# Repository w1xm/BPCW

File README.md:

# BPCW
1W UHF CW Trainer 

## Setup
The KiCAD project requires the W1MX-Parts project, see https://github.mit.edu/w1mx/W1MX-Parts.

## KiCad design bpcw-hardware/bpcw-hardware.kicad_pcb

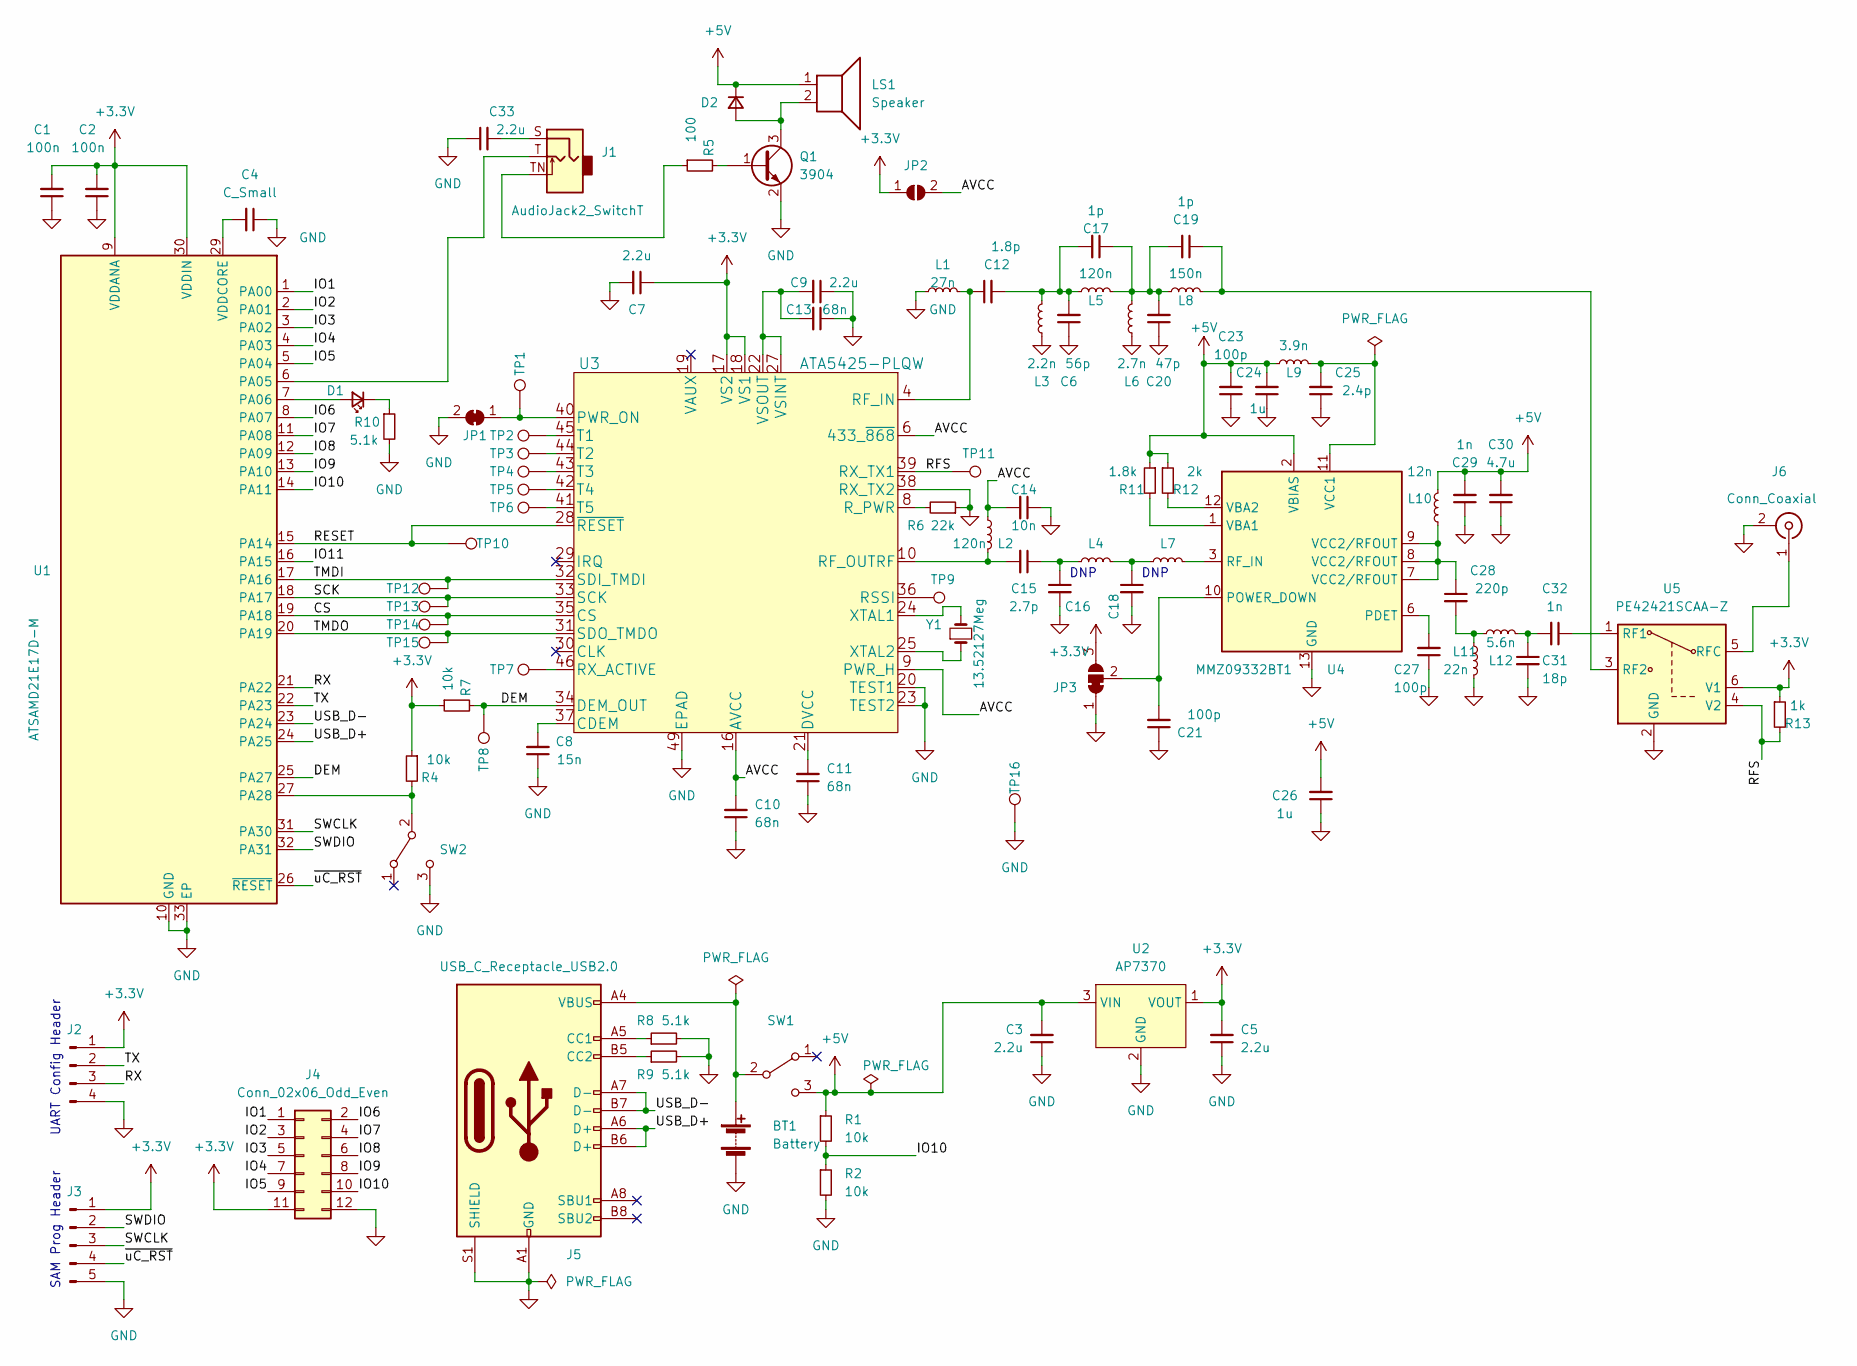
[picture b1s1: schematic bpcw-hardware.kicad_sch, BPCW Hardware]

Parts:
BT1: Battery; JST_XH_B2B-XH-A_1x02_P2.50mm_Vertical
C1, C2: 100n; C_0402_1005Metric
C3, C5, C7, C9, C33: 2.2u; C_0603_1608Metric
C4, C16, C18: C_Small; C_0402_1005Metric
C6: 56p; C_0402_1005Metric
C8: 15n; C_0402_1005Metric
C10, C11, C13: 68n; C_0402_1005Metric
C12: 1.8p; C_0402_1005Metric
C14: 10n; C_0402_1005Metric
C15: 2.7p; C_0402_1005Metric
C17, C19: 1p; C_0402_1005Metric
C20: 47p; C_0402_1005Metric
C21, C23, C27: 100p; C_0402_1005Metric
C24, C26: 1u; C_0603_1608Metric
C25: 2.4p; C_0402_1005Metric
C28: 220p; C_0402_1005Metric
C29, C32: 1n; C_0402_1005Metric
C30: 4.7u; C_0603_1608Metric
C31: 18p; C_0402_1005Metric
D1: LED_Small; LED_0603_1608Metric
D2: D_Small; D_SOD-323
J1: AudioJack2_SwitchT; CUI_MJ-3523-SMT
J2: Conn_01x04_Male; PinHeader_1x04_P2.54mm_Vertical
J3: Conn_01x05_Male; PinHeader_1x05_P2.54mm_Vertical
J4: Conn_02x06_Odd_Even; PinHeader_2x06_P2.54mm_Vertical
J5: USB_C_Receptacle_USB2.0; USB_C_Receptacle_GCT_USB4085
J6: Conn_Coaxial; SMA_Samtec_SMA-J-P-X-ST-EM1_EdgeMount
JP1: SolderJumper_2_Bridged; SolderJumper-2_P1.3mm_Bridged_Pad1.0x1.5mm
JP2: SolderJumper_2_Open; R_0402_1005Metric
JP3: SolderJumper_3_Bridged12; SolderJumper-3_P1.3mm_Bridged12_Pad1.0x1.5mm
L1: 27n; L_0603_1608Metric
L2, L5: 120n; L_0603_1608Metric
L3: 2.2n; L_0603_1608Metric
L4: 0; L_0603_1608Metric
L6: 2.7n; L_0603_1608Metric
L7, L9: 3.9n; L_0603_1608Metric
L8: 150n; L_0603_1608Metric
L10: 12n; L_0603_1608Metric
L11: 22n; L_0603_1608Metric
L12: 5.6n; L_0603_1608Metric
LS1: Speaker; CMT-9648-85T
Q1: 3904; SOT-23
R1, R2, R4, R7: 10k; R_0402_1005Metric
R5: 100; R_0402_1005Metric
R6: 22k; R_0402_1005Metric
R8, R9, R10: 5.1k; R_0402_1005Metric
R11: 1.8k; R_0402_1005Metric
R12: 2k; R_0402_1005Metric
R13: 1k; R_0402_1005Metric
SW1: SW_SPDT; 1825232-1; MPN 1825232-1
SW2: SW_SPDT; SS0750301F040P1A-Sideways; MPN 1825232-1
TP1, TP2, TP3, TP4, TP5, TP6, TP7, TP8, TP9, TP10, TP11, TP12, TP13, TP14, TP15, TP16: TestPoint; RCU-0603
U1: ATSAMD21E17D-M; QFN-32-1EP_5x5mm_P0.5mm_EP3.6x3.6mm
U2: AP7370; SOT-89-3
U3: ATA5425-PLQW; TQFN-48-1EP_7x7mm_P0.5mm_EP5.1x5.1mm_ThermalVias; MPN ATA5425
U4: MMZ09332BT1; QFN-12-1EP_3x3mm_P0.5mm_EP1.6x1.6mm_ThermalVias
U5: PE42421SCAA-Z; SOT-363_SC-70-6; MPN PE42421SCAA-Z
Y1: 13.52127Meg; HC49US-SMD; MPN ABLS-13.4916MHZ-10-R20-D-T

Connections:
+3V3: C1.2, C2.2, C5.2, C7.1, J2.1, J3.1, J4.11, JP2.1 (A), JP3.3 (B), R4.1, R7.1, R13.1, U1.9 (VDDANA), U1.30 (VDDIN), U2.1 (VOUT), U3.17 (VS2), U3.18 (VS1), U5.6 (V1)
+5V: C3.2, C23.2, C24.2, C26.2, C29.2, C30.2, D2.1 (K), L9.1, L10.2, LS1.1, R1.1, R11.1, R12.1, SW1.3 (C), U2.3 (VIN), U4.2 (VBIAS)
/AVCC: C10.2, C14.2, JP2.2 (B), L2.1, U3.6 (433_~868), U3.9 (PWR_H), U3.16 (AVCC)
/CS: TP14.1, U1.19 (PA18), U3.35 (CS)
/DEM: R7.2, TP8.1, U1.25 (PA27), U3.34 (DEM_OUT)
/IO1: J4.1, U1.1 (PA00)
/IO2: J4.3, U1.2 (PA01)
/IO3: J4.5, U1.3 (PA02)
/IO4: J4.7, U1.4 (PA03)
/IO5: J4.9, U1.5 (PA04)
/IO6: J4.2, U1.8 (PA07)
/IO7: J4.4, U1.11 (PA08)
/IO8: J4.6, U1.12 (PA09)
/IO9: J4.8, U1.13 (PA10)
/IO10: J4.10, R1.2, R2.1, U1.14 (PA11)
/IO11: U1.16 (PA15)
/RESET: TP10.1, U1.15 (PA14), U3.28 (~RESET)
/RFS: R13.2, TP11.1, U3.39 (RX_TX1), U5.4 (V2)
/RX: J2.3, U1.21 (PA22)
/SCK: TP13.1, U1.18 (PA17), U3.33 (SCK)
/SWCLK: J3.3, U1.31 (PA30)
/SWDIO: J3.2, U1.32 (PA31)
/TMDI: TP12.1, U1.17 (PA16), U3.32 (SDI_TMDI)
/TMDO: TP15.1, U1.20 (PA19), U3.31 (SDO_TMDO)
/TX: J2.2, U1.22 (PA23)
/USB_D+: J5.A6 (D+), J5.B6 (D+), U1.24 (PA25)
/USB_D-: J5.A7 (D-), J5.B7 (D-), U1.23 (PA24)
/~uC_RST: J3.4, U1.26 (~RESET)
GND: BT1.2 (-), C1.1, C2.1, C3.1, C4.1, C5.1, C6.1, C7.2, C8.1, C9.1, C10.1, C11.1, C13.1, C14.1, C16.2, C18.2, C20.1, C21.1, C23.1, C24.1, C25.1, C26.1, C27.1, C29.1, C30.1, C31.2, C33.1, J2.4, J3.5, J4.12, J5.A1 (GND), J5.A12 (GND), J5.B1 (GND), J5.B12 (GND), J5.S1 (SHIELD), J6.2 (Ext), JP1.2 (B), JP3.1 (A), L1.1, L3.1, L6.1, L11.1, Q1.2 (E), R2.2, R6.1, R8.2, R9.2, R10.2, SW2.3 (C), TP16.1, U1.10 (GND), U1.28 (GND), U1.33 (EP), U2.2 (GND), U3.20 (TEST1), U3.23 (TEST2), U3.38 (RX_TX2), U3.49 (EPAD), U4.13 (GND), U5.2 (GND)
unnamed: BT1.1 (+), J5.A4 (VBUS), J5.A9 (VBUS), J5.B4 (VBUS), J5.B9 (VBUS), SW1.2 (B)
unnamed: C4.2, U1.29 (VDDCORE)
unnamed: C8.2, U3.37 (CDEM)
unnamed: C11.2, U3.21 (DVCC)
unnamed: C12.1, L1.2, U3.4 (RF_IN)
unnamed: C6.2, C12.2, C17.2, L3.2, L5.1
unnamed: C9.2, C13.2, U3.22 (VSOUT), U3.27 (VSINT)
unnamed: C15.1, C16.1, L4.1
unnamed: C15.2, L2.2, U3.10 (RF_OUTRF)
unnamed: C17.1, C19.2, C20.2, L5.2, L6.2, L8.1
unnamed: C18.1, L4.2, L7.1
unnamed: C19.1, L8.2, U5.3 (RF2)
unnamed: C21.2, JP3.2 (C), U4.10 (POWER_DOWN)
unnamed: C25.2, L9.2, U4.11 (VCC1)
unnamed: C27.2, U4.6 (PDET)
unnamed: C28.1, L10.1, U4.7 (VCC2/RFOUT), U4.8 (VCC2/RFOUT), U4.9 (VCC2/RFOUT)
unnamed: C28.2, L11.2, L12.2
unnamed: C31.1, C32.2, L12.1
unnamed: C32.1, U5.1 (RF1)
unnamed: C33.2, J1.S
unnamed: D1.1 (K), R10.1
unnamed: D1.2 (A), U1.7 (PA06)
unnamed: D2.2 (A), LS1.2, Q1.3 (C)
unnamed: J1.T, U1.6 (PA05)
unnamed: J1.TN, R5.1
unnamed: J5.A5 (CC1), R8.1
unnamed: J5.B5 (CC2), R9.1
unnamed: J6.1 (In), U5.5 (RFC)
unnamed: JP1.1 (A), TP1.1, U3.40 (PWR_ON)
unnamed: L7.2, U4.3 (RF_IN)
unnamed: Q1.1 (B), R5.2
unnamed: R4.2, SW2.2 (B), U1.27 (PA28)
unnamed: R6.2, U3.8 (R_PWR)
unnamed: R11.2, U4.1 (VBA1)
unnamed: R12.2, U4.12 (VBA2)
unnamed: TP2.1, U3.45 (T1)
unnamed: TP3.1, U3.44 (T2)
unnamed: TP4.1, U3.43 (T3)
unnamed: TP5.1, U3.42 (T4)
unnamed: TP6.1, U3.41 (T5)
unnamed: TP7.1, U3.46 (RX_ACTIVE)
unnamed: TP9.1, U3.36 (RSSI)
unnamed: U3.24 (XTAL1), Y1.2
unnamed: U3.25 (XTAL2), Y1.1

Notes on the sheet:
UART Config Header
SAM Prog Header
DNP

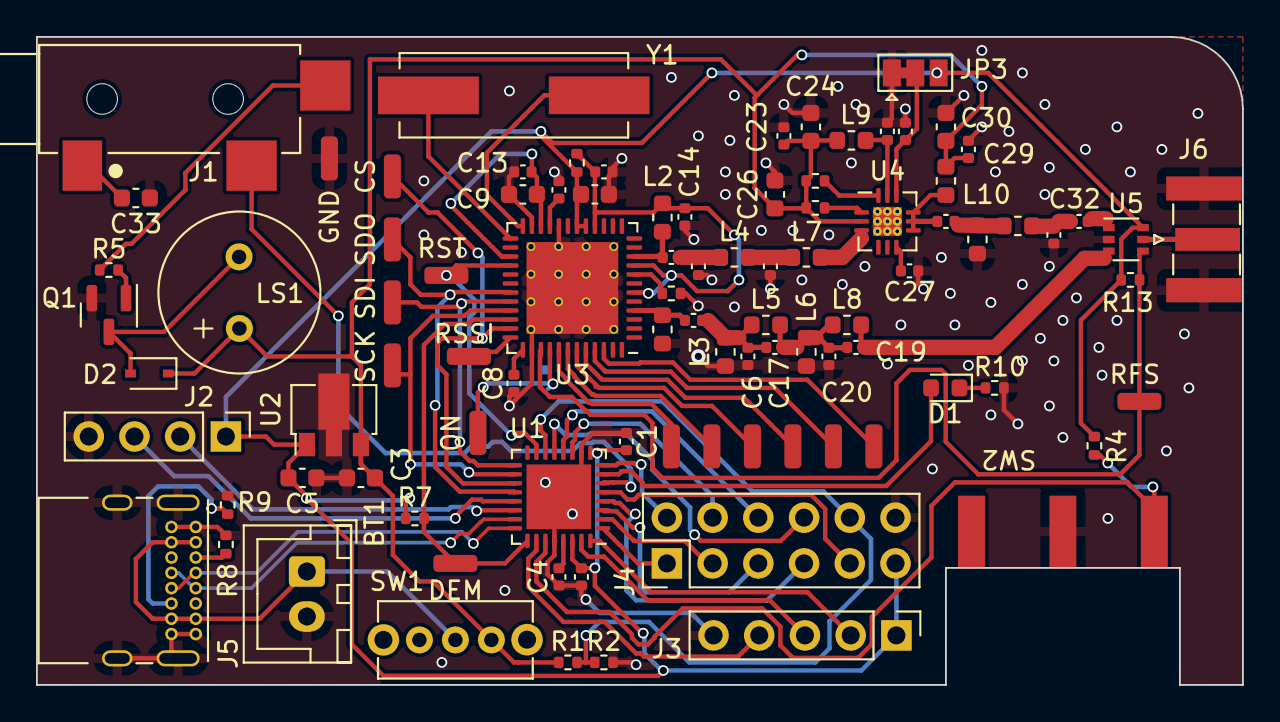
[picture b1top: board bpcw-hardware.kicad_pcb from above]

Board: 2 copper layers, 67.0 x 36.0 mm, 94 parts (1 on the bottom side), 72 nets.

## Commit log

2024-02-22 Move files over
2024-02-22 Fix photo
